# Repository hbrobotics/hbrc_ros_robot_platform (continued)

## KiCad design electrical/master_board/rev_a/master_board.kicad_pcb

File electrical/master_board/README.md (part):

<!--
MIT License

Copyright 2020 Home Brew Robotics Club

Permission is hereby granted, free of charge, to any person obtaining a copy of this
software and associated documentation files (the "Software"), to deal in the Software
without restriction, including without limitation the rights to use, copy, modify,
merge, publish, distribute, sublicense, and/or sell copies of the Software, and to
permit persons to whom the Software is furnished to do so, subject to the following
conditions:

The above copyright notice and this permission notice shall be included in all copies
or substantial portions of the Software.

THE SOFTWARE IS PROVIDED "AS IS", WITHOUT WARRANTY OF ANY KIND, EXPRESS OR IMPLIED,
INCLUDING BUT NOT LIMITED TO THE WARRANTIES OF MERCHANTABILITY, FITNESS FOR A PARTICULAR
PURPOSE AND NONINFRINGEMENT. IN NO EVENT SHALL THE AUTHORS OR COPYRIGHT HOLDERS BE LIABLE
FOR ANY CLAIM, DAMAGES OR OTHER LIABILITY, WHETHER IN AN ACTION OF CONTRACT, TORT OR
OTHERWISE, ARISING FROM, OUT OF OR IN CONNECTION WITH THE SOFTWARE OR THE USE OR OTHER
DEALINGS IN THE SOFTWARE.
-->
<!-- <<<<<<<<<<<<<<<<<<<<<<<<<<<<<<<<<<<<< 100 characters >>>>>>>>>>>>>>>>>>>>>>>>>>>>>>>>>>>>>> -->

# HR2 Master PCB Board

This is the common design information that is pretty applicable across all revisions
of the HR2 Master PCB Board.
The intention is to always use a higher end STM Nucleo-144 development board
as the embedded microcontroller.
This also allows processor upgrades to occur when newer Nucleo-144 boards come out
by simply upgrading to a newer Nucleo-144 board.
The higher end chips in the STM32Fxxx series of processors try to maintain peripheral
pin mappings across all versions of the 144-LQFP (144 pin Low profile Quad Flat Package.)
Time will tell how good ST Microelectronics is at adhering to this goal.
The nominal Nucleo-144 selected for revision A of the Master board is the Nucleo144-767ZI.
This may change over time with subsequent PCB board revisions.
g
It is a strong goal of the HR2 support the development of development boards that
plug onto the Nucleo-144.
The Nucleo-144 has two groups of connectors:

* Morpho Connectors:
  The Nucleo-144 has two Morpho connectors are called CN11 and CN12,
  each of which is a 2x35 pin connector.
  In general, the Morpho connectors connect to almost of the pins
  associated with STM32F microcontroller soldered to the Nucleo-144 board.
  The Nucleo-144 board ships without having either of the CN11 and CN12 connectors populated.
  It is necessary to solder connectors for CN11 and CN12.
  The HR2 master PCB sits under the Nucleo-144 and uses two female 2x35 headers to connect to the
  Nucleo-144 Morpho connectors.
  For the HR2, the Nucleo-144 is sufficiently big that it needs to positioned
  above the HR2 drive motors.
  For this reason, the Nucleo-144 needs long pins to bridge the distance
  between the CN11/CN12 connectors and to the master PCB.
  This is accomplished with two 2x35 male "wire-wrap" pin headers that are soldered to the
  bottom of the Nucleo-144 in CN11 and CN12.
  (Wire-wrap was a popular technology for prototyping electronics back in the 70's and 80's
  and it is still used occasionally to this day.)
  The Morpho connectors are exclusively dedicated to be used to connect the Nucleo-144
  to the HR2 master PCB.

* Zio Connectors:
  The Nucleo-144 has four Zio female pin connectors are called CN7 through CN10.
  These four connectors are sized and spaced to be compatible with Arduino shields.
  The difference is that while Arduino shields only use pin headers that are 1 wide,
  the Zio connectors are 2 pins wide.
  The extra row on each connector provides many more connectivity options
  than just simple Arduino pin connectors that are just 1 pin wide do.
  Despite these extra pins,
  the CN11/CN12 Morpho connectors still have pins than the CN7-CN10 Zio pins.

The ultimate goal of the HR2 is to support daughter boards that plug onto the Zio connectors.

The are 4 classes of daughter boards supported by the HR2.
Two of these classes use the Zio connectors and two do not.

* Arduino Shields (uses Zio connectors):
  An Arduino shield has 3 categories of pins:

  * Power/Miscellaneous Pins:
    The power and miscellaneous pins are RESET, 3.3V, 5V, GND, and VIN.
    These pins are easy to deal with and are not really mentioned any further in this document.

  * Digital Pins:
    There are 18 digital I/O pins named D0-D15.

  * Analog Pins:
    There 6 "analog" pins named A0-A5 that can used as analog-to-digital inputs
    or as digital I/O pins.
    Two of the "analog" pins (D4 and D5) are connected to an I2C peripheral.

  There are literally hundreds of Arduino shields that have been developed over the years.
  While  many of these Arduino shields are pretty mediocre, some of them are quite excellent.

* FPGA Daughter Board (uses Zio connectors):
  An FPGA  (Field Programmable Gate Array) daughter board is a PCB with an FPGA chip on it.
  The goal is to either allow the FPGA to totally control the robot or to partially control
  the robot in conjunction with the Nucleo-144 microcontroller.
  In addition, there is no particular reason why the FPGA should not be able to additionally host
  an Arduino shield on top if it so desires.

* Mikrobus Click Boards (does not use Zio connectors):

  The MikroElectronica company has created 20-pin standard peripheral boards
  that is called the MikroBus Click boards.
  These boards power, I2C, SPI, UART, and other pins.
  The come in three sizes -- small, medium and large.
  These 25.4mm wide (i.e. 1 inch) and 28.6mm (small), 42.9mm (medium), and 57.15mm (large).
  The HR2 has 2 Mikrobus connectors -- one small and one medium.
  A large can be plugged into the medium MikroBus connector on the HR2,
  but it will stick out of the robot.
  There are literally hundreds of MikroBus boards.

* Seeed Studio Grove Boards (does not use Zio connectors):
  Seeed Studio has come up with a huge library of peripheral boards that use a 4-pin
  proprietary connector.
  Two of the pins are power and ground and the other two vary from board to board.
  They fall into three broad categories:

  * Digital/Analog I/O: 2 pins of either digital and/or analog input or output.
    
  * I2C bus: 2 pins of I2C bus.

  * Serial: 2 pins of serial I/O (i.e. RX/TX.)

  The are 7 locations to mount Grove boards on the HR2.

The bottom line is that there many expansion opportunities for the HR2.

The following pin terminology is introduced.

* Arduino Pins:
  The Arduino signal pins are the pins that are reserved to connect to an Arduino shield.
  As mentioned above,
  the pins are further sub-divided into "analog" pins (A0-A5), and "digital" pins (D0-D13).
  Note that the "analog" pins can be connected to an A/D converter,
  but they can also be used as digital I/O pins.
  Two of the "analog" pins are bound to an I2C peripheral.
  There are 6 "analog" pins and 14 "digital" pins, for a total of 20 Arduino pins.

* Daughter Pins:
  The daughter pins are the remaining signal pins on the Zio connectors that are not
  are not Arduino Pins.
  It turns out that there are 45 dauhgter pins.

* Morpho Pins:
  The Morpho pins are the signal pins that are routed to the Morpho connectors
  but not also routed to the Zio connectors.
  It turns out that there are 17 Morpho pins.

* Nucleo Pins:
  The Nucleo-144 development board connects also connects some of its signal wires
  to the Morpho/Zio connectors.
  This is to be expected.
  Most of these pins are for the Ethernet connector, USB connector, and the ST-link signals.
  With three exceptions, Nucleo pins only connect to the Morph pins mentioned immeidately above.
  The three exceptions are:

  * PA7:
    PA7 is connected to the Ethernet interface chip.
    If you want to use the Ethernet interface,
    you must not attempt to plug in an Arduino shield that also needs to use D11.

  * PB0:
    PB0 is connected to LED called LD1.
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
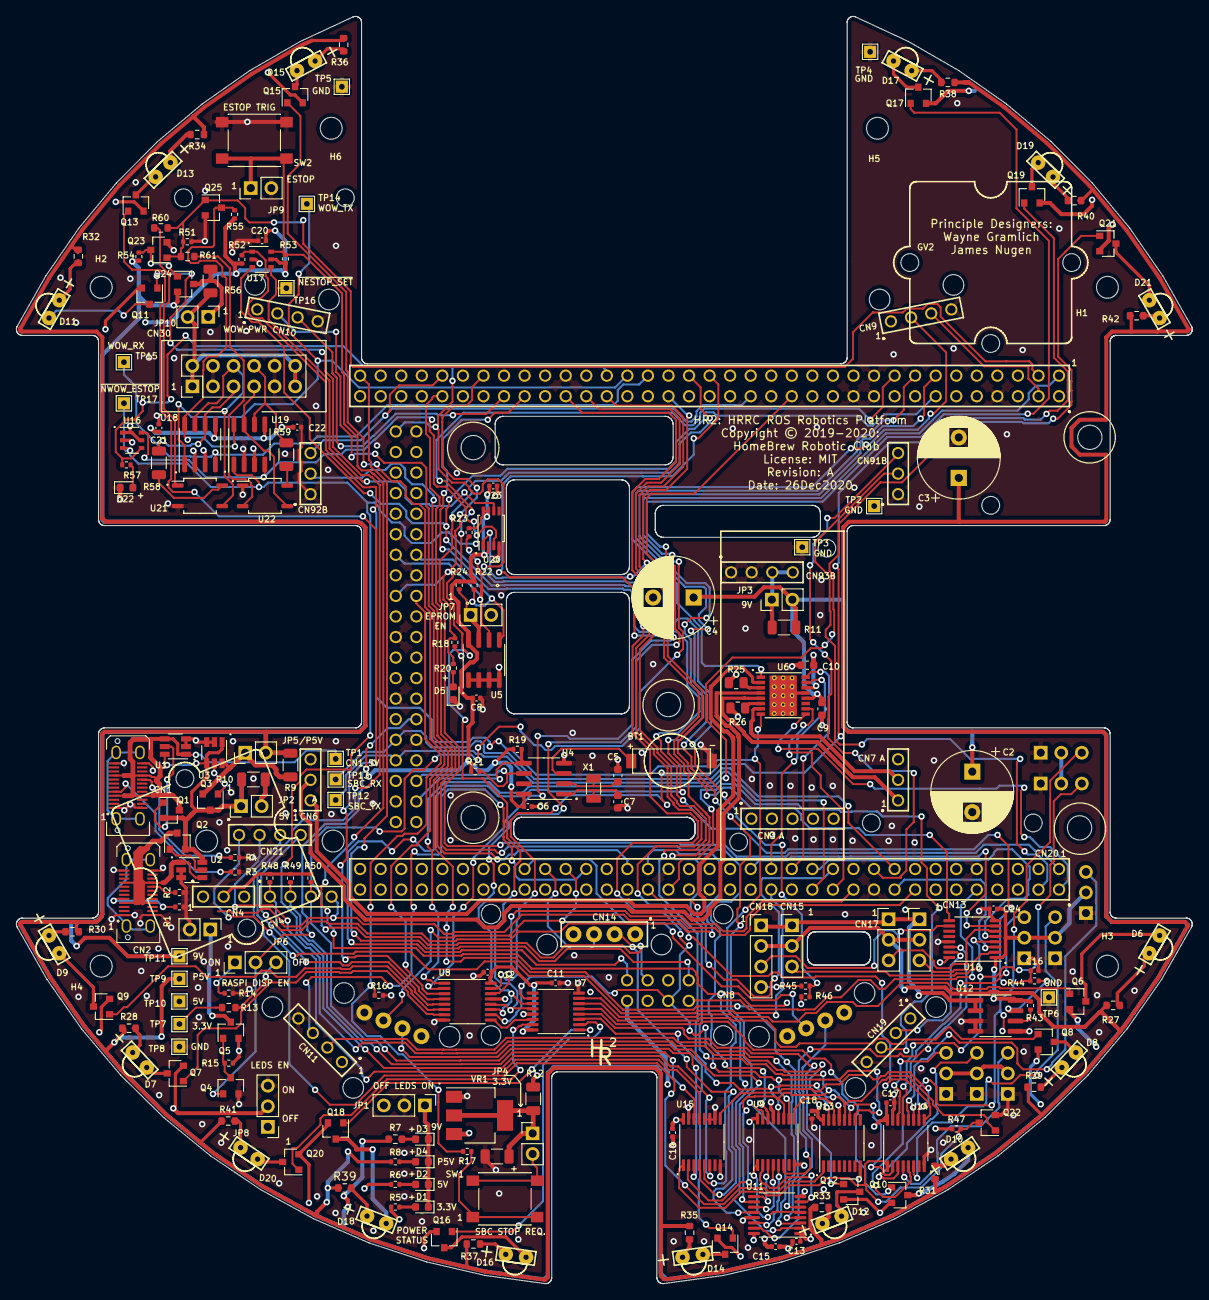
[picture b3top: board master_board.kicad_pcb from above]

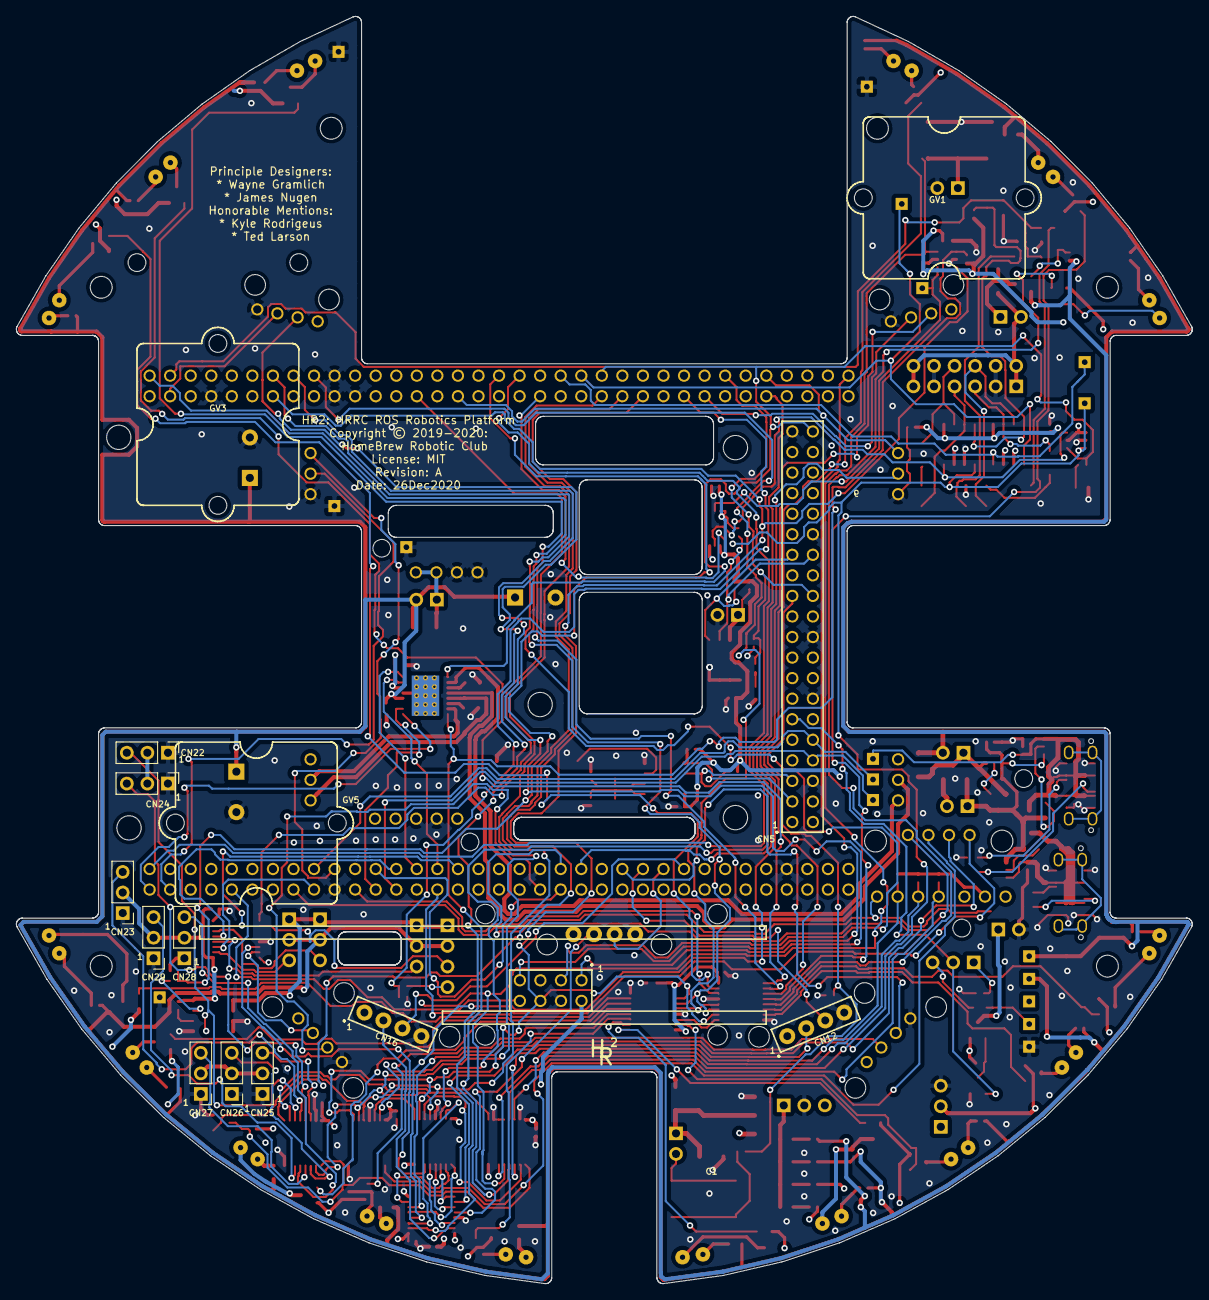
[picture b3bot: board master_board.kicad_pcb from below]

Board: 4 copper layers, 145.3 x 156.6 mm, 226 parts (13 on the bottom side), 198 nets.

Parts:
BT1: COIN_HOLDER6.8R;TE1376164-1; TE1376164-1_COINHOLDER6.8
C1: Ta22µF6.3V;3216; C_1206_3216Metric
C2, C4: 470µF,25Vmin;D10P5H13max; CP_Radial_D10.0mm_P5.00mm
C3: 1000µF@10Vmin;D10P5H13max; CP_Radial_D10.0mm_P5.00mm
C5, C7: 15pF;1608; C_0603_1608Metric
C6, C8, C11, C12, C13, C14, C15, C17, C18, C19, C20, C21, C22, C23: 0.1µF;1005; C_0402_1005Metric
C9: 10µF;1608; C_0603_1608Metric
C10: 2.2µF6.3V;1608; C_0603_1608Metric
C16: 0.01µF;1005; C_0402_1005Metric
CN1: USB-C;USB-C,POGND; USB_C_Receptacle_JAE_DX07S024WJ3R400
CN2: USB-C;USB-C; USB_C_Receptacle_JAE_DX07S024WJ3R400
CN3: POLOLU_U3V70F9;F1x4+F1x5; U3V70xMATE_F1x4+F1x5
CN4: RPI_DSP_PWR;M1x2; PinHeader_1x02_P2.54mm_Vertical
CN5: RASPI;F2X20; RASPI_F2X20
CN6, CN7: HR2_ENCODER;2xF1x3; ENCODER_2xF1x3
CN8: STADAPTER;F2x4; STADAPTER_F2x4
CN9, CN10: HCSR04LP;F1X4; HCSR04_F1x4H
CN11, CN19: HCSR04LP;F1X4; HCSR04_F1x4
CN12, CN14, CN16: HCSR04LP;F1X4; HCSR04_F1x4LP
CN13, CN15, CN17: SERVO;M1x3; PinHeader_1x03_P2.54mm_Vertical
CN18: SERVO;M1x4; PinHeader_1x04_P2.54mm_Vertical
CN20: NUCLEO-F767ZI;2xF2x35; NUCLEO_F767ZI_2xF2x35
CN21: LIDAR_ADAPTER;2xF1x4_F1x3; LIDAR_ADAPTER_2xF1x4_F1x3
CN22, CN23, CN24, CN25, CN26, CN27, CN28, CN29: SENSE;M1x3; PinHeader_1x03_P2.54mm_Vertical
CN30: WOW_OUT;M2x6S; PinHeader_2x06_P2.54mm_Vertical_Shrouded
D1, D2, D3, D4, D5: LEDGRN;1608; LED_0603_1608Metric
D6, D7, D8, D9, D10, D11, D12, D13, D14, D15, D16, D17, D18, D19, D20, D21: LED;GRNRA; LED_GRNRA
D22: REDLED;1608; LED_0603_1608Metric
GV1, GV2, GV3, GV4, GV5: GROVE;20x20; GROVE20x20
H1, H2, H3, H4, H5, H6: HOLE;M2.5; MountingHole_2.7mm_M2.5
JP1, JP8: LED_EN;M1x3; PinHeader_1x03_P2.54mm_Vertical
JP2, JP3, JP4, JP5, JP10: SHUNT;M1x2; PinHeader_1x02_P2.54mm_Vertical
JP6: RPI_DISP_EN;M1x3; PinHeader_1x03_P2.54mm_Vertical
JP7: JUMPER;M1x2; PinHeader_1x02_P2.54mm_Vertical
JP9: EXT_ESTOP;M1x2; PinHeader_1x02_P2.54mm_Vertical
Q1, Q2, Q3: NFET_3A_GSD;SOT23; SOT-23
Q4, Q6, Q7, Q8, Q9, Q10, Q11, Q12, Q13, Q14, Q15, Q16, Q17, Q18, Q19, Q20, Q21, Q22, Q23, Q25: 2N7002;SOT23; SOT-23
Q5, Q24: PFET_6A_GSD;SOT23; SOT-23
R1, R2, R3, R4: 10KΩ;1005; R_0402_1005Metric
R5, R20: 33Ω;1005; R_0402_1005Metric
R6, R8: 220Ω;1005; R_0402_1005Metric
R7: 560Ω;1608; R_0603_1608Metric
R9, R10, R11, R12, R56: 0Ω;3216; R_1206_3216Metric
R13: 100KΩ;1608; R_0603_1608Metric
R14, R15, R16, R18, R19, R21, R22, R23, R24, R43, R47, R48, R49, R50, R51, R52, R53, R54, R55: 100KΩ;1005; R_0402_1005Metric
R17, R44: 1KΩ;1005; R_0402_1005Metric
R25, R26: .16Ω.25W;2012; R_0805_2012Metric
R27, R28, R29, R30, R31, R32, R33, R34, R35, R36, R37, R38, R39, R40, R41, R42: 270Ω;1608; R_0603_1608Metric
R45: 2.2KΩ;1005; R_0402_1005Metric
R46: 3.3KΩ;1005; R_0402_1005Metric
R57: 120Ω;1005; R_0402_1005Metric
R58, R59: 120Ω.25W;3216; R_1206_3216Metric
R60, R61: 300Ω;1608; R_0603_1608Metric
SW1, SW2: BUTTON;6x6; SW_Push_1P1T_NO_6x6mm_H9.5mm
TP1: USB5V; TestPoint_THTPad_1.5x1.5mm_Drill0.7mm
TP2, TP3, TP4, TP5, TP6, TP8: GND; TestPoint_THTPad_1.5x1.5mm_Drill0.7mm
TP7: 3.3V; TestPoint_THTPad_1.5x1.5mm_Drill0.7mm
TP9: P5V; TestPoint_THTPad_1.5x1.5mm_Drill0.7mm
TP10: 5V; TestPoint_THTPad_1.5x1.5mm_Drill0.7mm
TP11: 9V; TestPoint_THTPad_1.5x1.5mm_Drill0.7mm
TP12: SPC_TX;M1x2; TestPoint_THTPad_1.5x1.5mm_Drill0.7mm
TP13: SBC_RX;M1x2; TestPoint_THTPad_1.5x1.5mm_Drill0.7mm
TP14: WOW_TX;M1x1; TestPoint_THTPad_1.5x1.5mm_Drill0.7mm
TP15: WOW_RX;M1x1; TestPoint_THTPad_1.5x1.5mm_Drill0.7mm
TP16: ~nESTOP_SET; TestPoint_THTPad_1.5x1.5mm_Drill0.7mm
TP17: ~nWOW_ESTOP;M1x1; TestPoint_THTPad_1.5x1.5mm_Drill0.7mm
U1, U2, U3: LM5050-1;TSOT-23-6; TSOT-23-6
U4: MCP7940;SOIC8; SOIC-8_3.9x4.9mm_P1.27mm
U5: CAT24C32;SOIC8; SOIC-8_3.9x4.9mm_P1.27mm
U6: DRV8833PWPR;HTSSOP16EP3.4x5; HTSSOP-16-1EP_4.4x5mm_P0.65mm_EP3.4x5mm_Mask3x3mm_ThermalVi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
U7, U8, U9, U13: SN74HC595;TSSOP16; TSSOP-16_4.4x5mm_P0.65mm
U10, U11: CD4504B;TTSOP16; TSSOP-16_4.4x5mm_P0.65mm
U12: ACS711;SOIC8; SOIC-8_3.9x4.9mm_P1.27mm
U14, U15: SN74HC165;TSSOP16; TSSOP-16_4.4x5mm_P0.65mm
U16, U17: 74x11G1;TSOP6; TSOP-6_1.65x3.05mm_P0.95mm
U18, U19: MCP2542;SOIC8; SOIC-8_3.9x4.9mm_P1.27mm
U20: 74LVC1G74;TSSOP8; TSSOP-8_3x3mm_P0.65mm
U21, U22: CPC1017N;SOP4W3.8L4.1; SOP-4_3.8x4.1mm_P2.54mm
VR1: AMS1117-3.3V800mA_GOI;SOT223; SOT-223-3_TabPin2
X1: 32.768kHz12.5pF;3.2x1.5; Crystal_SMD_3215-2Pin_3.2x1.5mm

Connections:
/3.3V: C6.1, C8.2, C11.1, C12.1, C13.1, C14.1, C15.1, C17.1, C18.1, C19.1, C20.2, C21.2, C22.2, C23.2, CN8.1, CN21.2, CN22.2, CN23.2, CN24.2, CN25.2, CN26.2, CN27.2, CN28.2, CN29.2, JP4.2, R5.1, R12.2, R13.1, R19.1, R21.1, R22.1, R23.1, R24.1, R43.1, R47.1, R48.1, R49.1, R50.1, R52.1, R53.1, R55.1, SW1.2, TP7.1, U4.8, U5.8, U7.16, U8.16, U9.16, U10.1, U11.1, U12.8, U13.16, U14.16, U15.16, U16.1, U16.5, U17.5, U18.5, U19.5, U20.2, U20.7, U20.8
/5V: CN3.4, CN3.5, CN5.2, CN5.4, CN6.3, CN7.3, CN9.1, CN10.1, CN11.1, CN12.1, CN14.1, CN16.1, CN19.1, CN20.1124, CN20.1207, CN21.1, JP2.2, Q5.2, R6.1, R10.2, R15.1, TP10.1, U10.16, U11.16, U18.3, U19.3, VR1.3
/9V: C2.1, C4.1, C9.1, JP3.2, Q24.2, R7.1, R11.2, R54.1, TP11.1, U6.12
/Connectors/DIO_IN_BRIDGE: U14.10, U15.9
/Connectors/DIO_SS: Q22.3, R47.2, U14.1, U15.1
/Connectors/LDR_EN: CN21.10, U13.1
/Connectors/LDR_ID0: CN21.4, R48.2, U15.13
/Connectors/LDR_ID1: CN21.5, R49.2, U15.14
/Connectors/LDR_ID2: CN21.6, R50.2, U15.3
/Connectors/LDR_SPIN: CN21.9, U13.15
/Connectors/SIG1: CN22.3, U14.11
/Connectors/SIG2: CN23.3, U14.12
/Connectors/SIG3: CN24.3, U14.13
/Connectors/SIG4: CN25.3, U14.14
/Connectors/SIG5: CN26.3, U14.3
/Connectors/SIG6: CN27.3, U14.4
/Connectors/SIG7: CN28.3, U14.5
/Connectors/SIG8: CN29.3, U14.6
/DIO_MISO: CN20.1150, U14.9
/DIO_MOSI: CN20.1162, U9.14
/DIO_SCK: CN20.1146, U9.11, U13.11, U14.2, U15.2
/ECHO1: CN9.3, CN20.1104
/ECHO2: CN10.3, CN20.1156
/ECHO3: CN11.3, CN20.1247
/ECHO4: CN12.3, CN20.1249
/ECHO5: CN14.3, CN20.1251
/ECHO6: CN16.3, CN20.1253
/ECHO7: CN19.3, CN20.1240
/ESTOP_CLR: CN20.1140, U20.1
/GND: BT1.2, C1.2, C2.2, C3.2, C4.2, C5.2, C6.2, C7.2, C8.1, C9.2, C10.2, C11.2, C12.2, C13.2, C14.2, C15.2, C16.2, C17.2, C18.2, C19.2, C20.1, C21.1, C22.1, C23.1, CN1.A1, CN1.A12, CN1.B1, CN1.B12, CN2.A1, CN2.A12, CN2.B1, CN2.B12, CN3.2, CN3.3, CN3.6, CN3.7, CN4.2, CN5.6, CN5.9, CN5.14, CN5.20, CN5.25, CN5.30, CN5.34, CN5.39, CN6.4, CN7.4, CN8.3, CN9.4, CN10.4, CN11.4, CN12.4, CN14.4, CN16.4, CN19.4, CN20.1108, CN20.1119, CN20.1120, CN20.1122, CN20.1149, CN20.1160, CN20.1209, CN20.1220, CN20.1232, CN20.1239, CN20.1254, CN20.1263, CN21.3, CN22.1, CN23.1, CN24.1, CN25.1, CN26.1, CN27.1, CN28.1, CN29.1, CN30.3, CN30.4, CN30.9, CN30.10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
/LDR_PWM: CN20.1241, CN21.11
/LDR_RX: CN20.1230, CN21.8
/LDR_TX: CN20.1216, CN21.7
/LED's/LED1: Q21.1, U8.15
/LED's/LED2: Q19.1, U8.1
/LED's/LED3: Q17.1, U8.2
/LED's/LED4: Q15.1, U8.3
/LED's/LED5: Q13.1, U8.4
/LED's/LED6: Q11.1, U8.5
/LED's/LED7: Q9.1, U8.6
/LED's/LED8: Q7.1, U8.7
/LED's/LED8_SER: U7.14, U8.9
/LED's/LED9: Q20.1, U7.15
/LED's/LED10: Q18.1, U7.1
/LED's/LED11: Q16.1, U7.2
/LED's/LED12: Q14.1, U7.3
/LED's/LED13: Q12.1, U7.4
/LED's/LED14: Q10.1, U7.5
/LED's/LED15: Q8.1, U7.6
/LED's/LED16: Q6.1, U7.7
/LED's/LEDS_GND: JP8.2, Q6.2, Q7.2, Q8.2, Q9.2, Q10.2, Q11.2, Q12.2, Q13.2, Q14.2, Q15.2, Q16.2, Q17.2, Q18.2, Q19.2, Q20.2, Q21.2
/LEDS_MOSI: CN20.1222, U8.14
/LEDS_SCLK: CN20.1101, U7.11, U8.11
/LMOTOR_CTL1: CN20.1227, U6.16
/LMOTOR_CTL2: CN20.1229, U6.15
/LQUAD_A: CN6.5, CN20.1243
/LQUAD_B: CN6.6, CN20.1132, CN20.1161
/Motors_Encoders/BMOTOR_OUT1: CN7.2, U6.7
/Motors_Encoders/BMOTOR_OUT2: CN7.1, U6.5
/Motors_Encoders/BMOTOR_SEN: R26.2, U6.6
/Motors_Encoders/LMOTOR_OUT1: CN6.1, U6.2
/Motors_Encoders/LMOTOR_OUT2: CN6.2, U6.4
/Motors_Encoders/LMOTOR_SEN: R25.2, U6.3
/P5V: C3.1, CN13.2, CN15.2, CN17.2, CN18.2, JP5.2, R8.1, R9.2, R27.1, R28.1, R29.1, R30.1, R31.1, R32.1, R33.1, R34.1, R35.1, R36.1, R37.1, R38.1, R39.1, R40.1, R41.1, R42.1, TP9.1
/Power/3.3V_LED: D1.2, R5.2
/Power/5V_LED: D2.2, R6.2
/Power/9V_LED: D3.2, R7.2
/Power/CN1_5V: CN1.A4, CN1.A9, CN1.B4, CN1.B9, Q1.3, TP1.1, U1.1, U1.4
/Power/CN2_5V: CN2.A4, CN2.A9, CN2.B4, CN2.B9, Q2.3, U2.1, U2.4
/Power/GATE1: Q1.1, U1.5
/Power/GATE2: Q2.1, U2.5
/Power/GATE3: Q3.1, U3.5
/Power/P5V_LED: D4.2, R8.2
/Power/SHUNT_3.3: C1.1, JP4.1, R12.1, VR1.2
/Power/SHUNT_5V: JP2.1, Q1.2, Q2.2, Q3.3, R10.1, U1.6, U2.6, U3.1, U3.4
/Power/SHUNT_9V: CN3.8, CN3.9, JP3.1, R11.1
/Power/SHUNT_P5V: JP5.1, Q3.2, R9.1, U3.6
/RMOTOR_CTL1: CN20.1202, U6.9
/RMOTOR_CTL2: CN20.1224, U6.10
/RQUAD_A: CN7.5, CN20.1204
/RQUAD_B: CN7.6, CN20.1219
/SBC_ALIVE: CN5.24, CN20.1157, R18.1, R20.1
/SERVO1: CN20.1128, U10.9
/SERVO2: CN20.1231, U10.7
/SERVO3: CN20.1225, U10.5
/SERVO4: CN20.1218, U10.3
/SERVO_CUR: C16.1, CN20.1135, R44.1
/SERVO_POS: CN20.1154, R45.2, R46.1
/SER_IO: U9.9, U13.14
/SPBC_RX: CN5.10, CN20.1217, TP13.1
/SPBC_TX: CN5.8, CN20.1226, TP12.1
/STL_RX: CN8.7, CN20.1210
/STL_TX: CN8.8, CN20.1169
/SWCLK: CN8.2, CN20.1115
/SWDIO: CN8.4, CN20.1113
/Single Board Computer/ID_SCL: CN5.28, R23.2, U5.6
/Single Board Computer/ID_SDA: CN5.27, R22.2, U5.5
/Single Board Computer/RPI_DSP_EN: CN5.11, JP6.2, Q4.1
/Single Board Computer/SBC_REQ: R17.1, SW1.1
/Single Board Computer/SBC_SCL: CN5.5, R21.2, U4.6
/Single Board Computer/SBC_SDA: CN5.3, R19.2, U4.5
/Single Board Computer/SBC_STOP: CN5.23, R16.1, R17.2
/Single Board Computer/VBAT: BT1.1, U4.3
/Single Board Computer/WP: JP7.1, R24.2, U5.7
/Single Board Computer/X1: C7.1, U4.1, X1.2
/Single Board Computer/X2: C5.1, U4.2, X1.1
/Sonars and Servos/SERVO1_5V: CN18.3, U10.10
/Sonars and Servos/SERVO2_5V: CN17.3, U10.6
/Sonars and Servos/SERVO3_5V: CN15.3, U10.4
/Sonars and Servos/SERVO4_5V: CN13.3, U10.2
/Sonars and Servos/SGND: CN13.1, CN15.1, CN17.1, CN18.1, U12.1, U12.2
/Sonars and Servos/TRIG1: U9.15, U11.3
/Sonars and Servos/TRIG1_5V: CN9.2, U11.2
/Sonars and Servos/TRIG2: U9.1, U11.5
/Sonars and Servos/TRIG2_5V: CN10.2, U11.4
/Sonars and Servos/TRIG3: U9.2, U11.7
/Sonars and Servos/TRIG3_5V: CN11.2, U11.6
/Sonars and Servos/TRIG4: U9.3, U11.9
/Sonars and Servos/TRIG4_5V: CN12.2, U11.10
/Sonars and Servos/TRIG5: U9.4, U11.11
/Sonars and Servos/TRIG5_5V: CN14.2, U11.12
/Sonars and Servos/TRIG6: U9.5, U11.14
/Sonars and Servos/TRIG6_5V: CN16.2, U11.15
/Sonars and Servos/TRIG7: U9.6, U10.14
/Sonars and Servos/TRIG7_5V: CN19.2, U10.15
/WOWBus/WOW_COMH: CN30.6, U18.7, U21.3
/WOWBus/WOW_COML: CN30.5, R58.2, U18.6
/WOWBus/WOW_COM_OPTO: R60.1, U21.1
/WOWBus/WOW_ESTOP_OPTO: R61.2, U22.2
/WOWBus/WOW_POW_OUT: CN30.1, CN30.2, CN30.11, CN30.12, JP10.2, R56.2
/WOWBus/WOW_STDBY: Q25.3, R55.2, U18.8, U19.8
/WOWBus/WOW_STOPH: CN30.7, U19.7, U22.3
/WOWBus/WOW_STOPL: CN30.8, R59.2, U19.6
/WOWBus/~NESTOP_SET: TP16.1, U17.4, U20.6
/WOWBus/~NHR2_ESTOP: U16.6, U19.4, U20.3
/WOWBus/~NWOW_EN: Q23.3, Q24.1, R54.2
/WOW_EN: CN20.1103, Q23.1, Q25.1, R51.1, R60.2, R61.1
/WOW_RX: CN20.1141, TP15.1, U18.4
/WOW_TX: CN20.1143, TP14.1, U18.1
/~DIO_NSS: CN20.1148, Q22.1, U9.12, U13.12
/~LEDS_NSS: CN20.1117, U7.12, U8.12
/~NBTN_ESTOP: JP9.1, R53.2, SW2.2, U15.5, U17.6
/~NESTOP: CN5.40, CN20.1145, R57.1, U6.1, U16.4
/~NMOTOR_FAULT: R52.2, U6.8, U15.4, U17.1
/~NRST: CN8.5, CN20.1114, U7.10, U8.10, U9.10, U13.10, U17.3
/~NWOW_ESTOP: TP17.1, U15.6, U16.3, U19.1
unnamed: C10.1, U6.14
unnamed: CN1.A5, R3.2
unnamed: CN1.B5, R4.2
unnamed: CN2.A5, R1.2
unnamed: CN2.B5, R2.2
unnamed: CN4.1, Q5.3
unnamed: CN18.4, R45.1
unnamed: CN20.1137, CN20.1201
unnamed: CN20.1223, CN20.1242
unnamed: D1.1, D2.1, D3.1, D4.1, JP1.1
unnamed: D5.2, R20.2
unnamed: D6.1, Q6.3
unnamed: D6.2, R27.2
unnamed: D7.1, Q7.3
unnamed: D7.2, R28.2
unnamed: D8.1, Q8.3
unnamed: D8.2, R29.2
unnamed: D9.1, Q9.3
unnamed: D9.2, R30.2
unnamed: D10.1, Q10.3
unnamed: D10.2, R31.2
unnamed: D11.1, Q11.3
unnamed: D11.2, R32.2
unnamed: D12.1, Q12.3
unnamed: D12.2, R33.2
unnamed: D13.1, Q13.3
unnamed: D13.2, R34.2
unnamed: D14.1, Q14.3
unnamed: D14.2, R35.2
unnamed: D15.1, Q15.3
unnamed: D15.2, R36.2
unnamed: D16.1, Q16.3
unnamed: D16.2, R37.2
unnamed: D17.1, Q17.3
unnamed: D17.2, R38.2
unnamed: D18.1, Q18.3
unnamed: D18.2, R39.2
unnamed: D19.1, Q19.3
unnamed: D19.2, R40.2
unnamed: D20.1, Q20.3
unnamed: D20.2, R41.2
unnamed: D21.1, Q21.3
unnamed: D21.2, R42.2
unnamed: D22.2, R57.2
unnamed: JP6.1, R14.1
unnamed: JP6.3, R13.2
unnamed: JP10.1, Q24.3, R56.1
unnamed: Q4.3, Q5.1, R15.2
unnamed: R43.2, U12.6
unnamed: R44.2, U12.7
unnamed: R58.1, U21.4
unnamed: R59.1, U22.4

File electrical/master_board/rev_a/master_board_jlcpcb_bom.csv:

"Comment","Designator","Footprint","LCSC Part #"
"Ta22uF6.3V;3216","C1, ","CASE-A","C135574",
"2.2uF6.3V;1608","C10, ","0603","C23630",
"0.01uF;1005","C16, ","0402","C15195",
"15pF;1608","C5, C7, ","0603","C1644",
"0.1uF;1005","C6, C8, C11, C12, C13, C14, C15, C17, C18, C19, C20, C21, C22, C23, ","0402","C1525",
"10uF;1608","C9, ","0603","C19702",
"LEDGRN;1608","D1, D2, D3, D4, D5, ","LED_0603","C72043",
"REDLED;1608","D22, ","LED_0603","C2286",
"NFET_3A_GSD;SOT23","Q1, Q2, Q3, ","SOT-23-3L","C20917",
"2N7002;SOT23","Q4, Q6, Q7, Q8, Q9, Q10, Q11, Q12, Q13, Q14, Q15, Q16, Q17, Q18, Q19, Q20, Q21, Q22, Q23, Q25, ","SOT-23-3","C8545",
"PFET_6A_GSD;SOT23","Q5, Q24, ","SOT-23-3","C141546",
"10KOhm;1005","R1, R2, R3, R4, ","0402","C25744",
"100KOhm;1608","R13, ","0603","C25803",
"100KOhm;1005","R14, R15, R16, R18, R19, R21, R22, R23, R24, R43, R47, R48, R49, R50, R51, R52, R53, R54, R55, ","0402","C25741",
"1KOhm;1005","R17, R44, ","0402","C11702",
".16Ohm.25W;2012","R25, R26, ","0805","C34388",
"270Ohm;1608","R27, R28, R29, R30, R31, R32, R33, R34, R35, R36, R37, R38, R39, R40, R41, R42, ","0603","C22966",
"2.2KOhm;1005","R45, ","0402","C25879",
"3.3KOhm;1005","R46, ","0402","C25890",
"33Ohm;1005","R5, R20, ","0402","C25105",
"120Ohm;1005","R57, ","0402","C25079",
"120Ohm.25W;3216","R58, R59, ","1206","C17909",
"220Ohm;1005","R6, R8, ","0402","C25091",
"300Ohm;1608","R60, R61, ","0603","C23025",
"560Ohm;1608","R7, ","0603","C23204",
"0Ohm;3216","R9, R10, R11, R12, R56, ","1206","C17888",
"BUTTON;6x6","SW1, SW2, ","SMD-4","C127509",
"LM5050-1;TSOT-23-6","U1, U2, U3, ","SOT-23-6L","C55266",
"CD4504B;TTSOP16","U10, U11, ","TSSOP-16","C233582",
"ACS711;SOIC8","U12, ","SOIC-8","C10681",
"SN74HC165;TSSOP16","U14, U15, ","HTSSOP-16","C201716",
"CPC1017N;SOP4W3.8L4.1","U21, U22, ","SOP-4","C261926",
"MCP7940;SOIC8","U4, ","SOIC-8","C7440",
"CAT24C32;SOIC8","U5, ","SOIC-8","C81193",
"DRV8833PWPR;HTSSOP16EP3.4x5","U6, ","HTSSOP-16","C50506",
"SN74HC595;TSSOP16","U7, U8, U9, U13, ","HTSSOP-16","C5948",
"AMS1117-3.3V800mA_GOI;SOT223","VR1, ","SOT-223","C6186",
"32.768kHz12.5pF;3.2x1.5","X1, ","SMD-3215","C32346",

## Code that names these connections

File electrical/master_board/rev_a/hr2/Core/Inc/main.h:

/* USER CODE BEGIN Header */
/**
  ******************************************************************************
  * @file           : main.h
  * @brief          : Header for main.c file.
  *                   This file contains the common defines of the application.
  ******************************************************************************
  * @attention
  *
  * <h2><center>&copy; Copyright (c) 2020 STMicroelectronics.
  * All rights reserved.</center></h2>
  *
  * This software component is licensed by ST under BSD 3-Clause license,
  * the "License"; You may not use this file except in compliance with the
  * License. You may obtain a copy of the License at:
  *                        opensource.org/licenses/BSD-3-Clause
  *
  ******************************************************************************
  */
/* USER CODE END Header */

/* Define to prevent recursive inclusion -------------------------------------*/
#ifndef __MAIN_H
#define __MAIN_H

#ifdef __cplusplus
extern "C" {
#endif

/* Includes ------------------------------------------------------------------*/
#include "stm32f7xx_hal.h"

/* Private includes ----------------------------------------------------------*/
/* USER CODE BEGIN Includes */

/* USER CODE END Includes */

/* Exported types ------------------------------------------------------------*/
/* USER CODE BEGIN ET */

/* USER CODE END ET */

/* Exported constants --------------------------------------------------------*/
/* USER CODE BEGIN EC */

/* USER CODE END EC */

/* Exported macro ------------------------------------------------------------*/
/* USER CODE BEGIN EM */

/* USER CODE END EM */

/* Exported functions prototypes ---------------------------------------------*/
void Error_Handler(void);

/* USER CODE BEGIN EFP */

/* USER CODE END EFP */

/* Private defines -----------------------------------------------------------*/
#define DIO_SCK_Pin GPIO_PIN_2
#define DIO_SCK_GPIO_Port GPIOE
#define DIO_NSS_Pin GPIO_PIN_4
#define DIO_NSS_GPIO_Port GPIOE
#define DIO_MOSO_Pin GPIO_PIN_5
#define DIO_MOSO_GPIO_Port GPIOE
#define DIO_MOSI_Pin GPIO_PIN_6
#define DIO_MOSI_GPIO_Port GPIOE
#define USER_BTN_Pin GPIO_PIN_13
#define USER_BTN_GPIO_Port GPIOC
#define MISC_SDA_Pin GPIO_PIN_0
#define MISC_SDA_GPIO_Port GPIOF
#define MISC_SCL_Pin GPIO_PIN_1
#define MISC_SCL_GPIO_Port GPIOF
#define A3_Pin GPIO_PIN_3
#define A3_GPIO_Port GPIOF
#define A4_SDA_Pin GPIO_PIN_5
#define A4_SDA_GPIO_Port GPIOF
#define FPGA_RX_Pin GPIO_PIN_7
#define FPGA_RX_GPIO_Port GPIOF
#define SERVO_POS_Pin GPIO_PIN_8
#define SERVO_POS_GPIO_Port GPIOF
#define ECHO2_Pin GPIO_PIN_9
#define ECHO2_GPIO_Port GPIOF
#define A5_SCL_Pin GPIO_PIN_10
#define A5_SCL_GPIO_Port GPIOF
#define MCO_Pin GPIO_PIN_0
#define MCO_GPIO_Port GPIOH
#define A1_Pin GPIO_PIN_0
#define A1_GPIO_Port GPIOC
#define RMII_MDC_Pin GPIO_PIN_1
#define RMII_MDC_GPIO_Port GPIOC
#define SERVO_CUR_Pin GPIO_PIN_2
#define SERVO_CUR_GPIO_Port GPIOC
#define A2_Pin GPIO_PIN_3
#define A2_GPIO_Port GPIOC
#define SERVO1_Pin GPIO_PIN_0
#define SERVO1_GPIO_Port GPIOA
#define RMII_REF_CLK_Pin GPIO_PIN_1
#define RMII_REF_CLK_GPIO_Port GPIOA
#define RMII_MDIO_Pin GPIO_PIN_2
#define RMII_MDIO_GPIO_Port GPIOA
#define A0_Pin GPIO_PIN_3
#define A0_GPIO_Port GPIOA
#define LQUAD_B_Pin GPIO_PIN_4
#define LQUAD_B_GPIO_Port GPIOA
#define D13_SCK_Pin GPIO_PIN_5
#define D13_SCK_GPIO_Port GPIOA
#define D12_MISO_Pin GPIO_PIN_6
#define D12_MISO_GPIO_Port GPIOA
#define D11_PWM_MOSI_Pin GPIO_PIN_7
#define D11_PWM_MOSI_GPIO_Port GPIOA
#define RMII_RXD0_Pin GPIO_PIN_4
#define RMII_RXD0_GPIO_Port GPIOC
#define RMII_RXD1_Pin GPIO_PIN_5
#define RMII_RXD1_GPIO_Port GPIOC
#define GRN_LED_Pin GPIO_PIN_0
#define GRN_LED_GPIO_Port GPIOB
#define RMOTOR_CTL2_Pin GPIO_PIN_1
#define RMOTOR_CTL2_GPIO_Port GPIOB
#define LEDS_MOSI_Pin GPIO_PIN_2
#define LEDS_MOSI_GPIO_Port GPIOB
#define FPGA_TX_Pin GPIO_PIN_7
#define FPGA_TX_GPIO_Port GPIOE
#define ECHO7_Pin GPIO_PIN_8
#define ECHO7_GPIO_Port GPIOE
#define D6_PWM_Pin GPIO_PIN_9
#define D6_PWM_GPIO_Port GPIOE
#define ECHO3_Pin GPIO_PIN_10
#define ECHO3_GPIO_Port GPIOE
#define D5_PWM_Pin GPIO_PIN_11
#define D5_PWM_GPIO_Port GPIOE
#define ECHO4_Pin GPIO_PIN_12
#define ECHO4_GPIO_Port GPIOE
#define D3_PWM_Pin GPIO_PIN_13
#define D3_PWM_GPIO_Port GPIOE
#define ECHO5_Pin GPIO_PIN_14
#define ECHO5_GPIO_Port GPIOE
#define ECHO6_Pin GPIO_PIN_15
#define ECHO6_GPIO_Port GPIOE
#define SERVO3_Pin GPIO_PIN_10
#define SERVO3_GPIO_Port GPIOB
#define SERVO4_Pin GPIO_PIN_11
#define SERVO4_GPIO_Port GPIOB
#define LIDAR_TX_Pin GPIO_PIN_12
#define LIDAR_TX_GPIO_Port GPIOB
#define LIDAR_RX_Pin GPIO_PIN_13
#define LIDAR_RX_GPIO_Port GPIOB
#define LD3_Pin GPIO_PIN_14
#define LD3_GPIO_Port GPIOB
#define SBC_TX_Pin GPIO_PIN_15
#define SBC_TX_GPIO_Port GPIOB
#define STL_RX_Pin GPIO_PIN_8
#define STL_RX_GPIO_Port GPIOD
#define STL_TX_Pin GPIO_PIN_9
#define STL_TX_GPIO_Port GPIOD
#define LQUAD_A_Pin GPIO_PIN_12
#define LQUAD_A_GPIO_Port GPIOD
#define LIDAR_PWM_Pin GPIO_PIN_13
#define LIDAR_PWM_GPIO_Port GPIOD
#define D10_PWM_NSS_Pin GPIO_PIN_14
#define D10_PWM_NSS_GPIO_Port GPIOD
#define D9_PWM_Pin GPIO_PIN_15
#define D9_PWM_GPIO_Port GPIOD
#define USB_PowerSwitchOn_Pin GPIO_PIN_6
#define USB_PowerSwitchOn_GPIO_Port GPIOG
#define USB_OverCurrent_Pin GPIO_PIN_7
#define USB_OverCurrent_GPIO_Port GPIOG
#define RQUAD_A_Pin GPIO_PIN_6
#define RQUAD_A_GPIO_Port GPIOC
#define RQUAD_B_Pin GPIO_PIN_7
#define RQUAD_B_GPIO_Port GPIOC
#define RMOTOR_CTL1_Pin GPIO_PIN_8
#define RMOTOR_CTL1_GPIO_Port GPIOC
#define A4_SDAC9_Pin GPIO_PIN_9
#define A4_SDAC9_GPIO_Port GPIOC
#define USB_VBUS__Pin GPIO_PIN_9
#define USB_VBUS__GPIO_Port GPIOA
#define USB_ID_Pin GPIO_PIN_10
#define USB_ID_GPIO_Port GPIOA
#define USB_DM_Pin GPIO_PIN_11
#define USB_DM_GPIO_Port GPIOA
#define USB_DP_Pin GPIO_PIN_12
#define USB_DP_GPIO_Port GPIOA
#define SWDIO_Pin GPIO_PIN_13
#define SWDIO_GPIO_Port GPIOA
#define SWCLK_Pin GPIO_PIN_14
#define SWCLK_GPIO_Port GPIOA
#define LEDS_NSS_Pin GPIO_PIN_15
#define LEDS_NSS_GPIO_Port GPIOA
#define LEDS_SCK_Pin GPIO_PIN_10
#define LEDS_SCK_GPIO_Port GPIOC
#define LEDS_MISO_Pin GPIO_PIN_11
#define LEDS_MISO_GPIO_Port GPIOC
#define WOW_EN_Pin GPIO_PIN_12
#define WOW_EN_GPIO_Port GPIOC
#define SBC_ALIVE_Pin GPIO_PIN_0
#define SBC_ALIVE_GPIO_Port GPIOD
#define INT1_Pin GPIO_PIN_1
#define INT1_GPIO_Port GPIOD
#define ECHO1_Pin GPIO_PIN_2
#define ECHO1_GPIO_Port GPIOD
#define ESTOP_CLR_Pin GPIO_PIN_3
#define ESTOP_CLR_GPIO_Port GPIOD
#define WOW_RX_Pin GPIO_PIN_5
#define WOW_RX_GPIO_Port GPIOD
#define WOW_TX_Pin GPIO_PIN_6
#define WOW_TX_GPIO_Port GPIOD
#define ESTOP_Pin GPIO_PIN_7
#define ESTOP_GPIO_Port GPIOD
#define D0_RX_Pin GPIO_PIN_9
#define D0_RX_GPIO_Port GPIOG
#define RMII_TX_EN_Pin GPIO_PIN_11
#define RMII_TX_EN_GPIO_Port GPIOG
#define RMII_TXD0_Pin GPIO_PIN_13
#define RMII_TXD0_GPIO_Port GPIOG
#define D1_TX_Pin GPIO_PIN_14
#define D1_TX_GPIO_Port GPIOG
#define SERVO2_Pin GPIO_PIN_3
#define SERVO2_GPIO_Port GPIOB
#define LMOTOR_CTL1_Pin GPIO_PIN_4
#define LMOTOR_CTL1_GPIO_Port GPIOB
#define LMOTOR_CTL2_Pin GPIO_PIN_5
#define LMOTOR_CTL2_GPIO_Port GPIOB
#define SBC_RX_Pin GPIO_PIN_6
#define SBC_RX_GPIO_Port GPIOB
#define BLUE_LED_Pin GPIO_PIN_7
#define BLUE_LED_GPIO_Port GPIOB
#define D15_Pin GPIO_PIN_8
#define D15_GPIO_Port GPIOB
#define D14_Pin GPIO_PIN_9
#define D14_GPIO_Port GPIOB
#define INT0_Pin GPIO_PIN_0
#define INT0_GPIO_Port GPIOE
#define LQUAD_BE1_Pin GPIO_PIN_1
#define LQUAD_BE1_GPIO_Port GPIOE
/* USER CODE BEGIN Private defines */

/* USER CODE END Private defines */

#ifdef __cplusplus
}
#endif

#endif /* __MAIN_H */

/************************ (C) COPYRIGHT STMicroelectronics *****END OF FILE****/

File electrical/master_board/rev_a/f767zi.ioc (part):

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PB13.GPIOParameters=GPIO_Label
PC7.GPIOParameters=GPIO_Label
PC12.Signal=UART5_TX
PB14.GPIO_Label=LD3 [Red]
PG6.GPIO_Label=USB_PowerSwitchOn [STMPS2151STR_EN]
PA14.GPIO_Label=TCK
PG3.GPIOParameters=GPIO_Label,GPIO_ModeDefaultOutputPP
PG0.Signal=GPIO_Output
PC6.GPIO_Label=LD_BEAM_EN
PB13.Signal=ETH_TXD1
PG13.Signal=ETH_TXD0
PG2.GPIOParameters=GPIO_Label,GPIO_ModeDefaultOutputPP
PG15.GPIO_Label=_ESTOP2
PG2.GPIO_ModeDefaultOutputPP=GPIO_MODE_OUTPUT_PP
PC7.Signal=GPIO_Output
PH1/OSC_OUT.Signal=RCC_OSC_OUT
PE1.Signal=UART8_TX
PF10.GPIO_Label=ESTOPPED
PB3.Mode=Trace_Asynchronous_SW
PF1.GPIO_Label=PCB_ID1
PG14.Mode=Asynchronous
PG1.GPIOParameters=GPIO_Label,GPIO_ModeDefaultOutputPP
PC4.GPIO_Label=RMII_RXD0 [LAN8742A-CZ-TR_RXD0]
PG12.GPIOParameters=GPIO_Label
PA8.Signal=USB_OTG_FS_SOF
PF3.Signal=GPIO_Input
PG0.GPIO_PuPd=GPIO_NOPULL
Mcu.Package=LQFP144
PG13.GPIOParameters=GPIO_Label
PA10.Signal=USART1_RX
PB14.GPIOParameters=GPIO_Label
PC4.GPIOParameters=GPIO_Label
PG12.Signal=GPIO_Input
PA15.GPIOParameters=GPIO_Label
PG9.Signal=USART6_RX
PC13.Signal=GPXTI13
PE1.Mode=Asynchronous
PG9.Mode=Asynchronous
PC6.Signal=GPIO_Output
PA11.GPIO_Label=USB_DM
PC11.GPIOParameters=GPIO_Label
PG13.GPIO_Label=RMII_TXD0 [LAN8742A-CZ-TR_TXD0]
PG10.Signal=GPIO_Output
PE8.Mode=Asynchronous
PA3.Mode=Asynchronous
PA8.GPIO_Label=USB_SOF [TP1]
PA9.Signal=USART1_TX
PB10.Signal=USART3_TX
PA0/WKUP.Mode=Asynchronous
PF3.GPIOParameters=GPIO_Label
PG6.GPIOParameters=GPIO_Label
PB14.Signal=GPIO_Output
PC12.Mode=Asynchronous
PF2.GPIOParameters=GPIO_Label
PA1.Mode=Asynchronous
PE8.Signal=UART7_TX
PG7.GPIO_Label=USB_OverCurrent [STMPS2151STR_FAULT]
PC10.GPIOParameters=GPIO_Label
PA13.Mode=Trace_Asynchronous_SW
PC9.GPIOParameters=GPIO_Label
PC7.GPIO_Label=LD_MTR_EN
PG15.GPIOParameters=GPIO_Label
PA14.GPIOParameters=GPIO_Label
PA11.Signal=USB_OTG_FS_DM
PF10.GPIOParameters=GPIO_Label
PF0.GPIO_Label=PCB_ID0
PG0.GPIOParameters=GPIO_PuPd,GPIO_Label,GPIO_ModeDefaultOutputPP
PC15/OSC32_OUT.Signal=RCC_OSC32_OUT
PG3.GPIO_Label=LED3
PD2.Signal=UART5_RX
PA7.GPIOParameters=GPIO_Label
PC1.Signal=ETH_MDC
PG10.GPIO_Label=_ESTOP0
PG7.GPIOParameters=GPIO_Label
PH0/OSC_IN.GPIOParameters=GPIO_Label
PG6.Signal=GPIO_Output
Mcu.UserName=STM32F767ZITx
PG2.Signal=GPIO_Output
PC10.Signal=GPIO_Output
RCC.SYSCLKSourceVirtual=RCC_SYSCLKSOURCE_PLLCLK
PF0.GPIOParameters=GPIO_Label
PA12.GPIOParameters=GPIO_Label
PA9.GPIOParameters=GPIO_PuPd,GPIO_Mode
PA11.GPIOParameters=GPIO_Label
PA0/WKUP.Signal=UART4_TX
PC13.GPIO_Label=USER_Btn [B1]
PB13.GPIO_Label=RMII_TXD1 [LAN8742A-CZ-TR_TXD1]
PB11.Signal=USART3_RX
PG11.Signal=GPIO_Output
PG15.Signal=GPIO_Input
PA15.GPIO_Label=_ESTOP_RESET
PA12.Signal=USB_OTG_FS_DP
PC1.GPIOParameters=GPIO_Label
PF1.GPIOParameters=GPIO_Label
PG3.GPIO_ModeDefaultOutputPP=GPIO_MODE_OUTPUT_PP
PF11.GPIO_Label=_ESTOP_BUS
PA8.GPIOParameters=GPIO_Label
PG0.GPIO_ModeDefaultOutputPP=GPIO_MODE_OUTPUT_PP
PA9.GPIO_Mode=GPIO_MODE_AF_PP
RCC.HSE_VALUE=16000000
PA14.Mode=Trace_Asynchronous_SW
PF11.Signal=GPIO_Input
PC11.GPIO_Label=LDR_RX
PB3.GPIOParameters=GPIO_Label
PB7.Signal=GPIO_Output
PF11.GPIOParameters=GPIO_Label
PA13.GPIOParameters=GPIO_Label
PB7.GPIO_Label=LD2 [Blue]
PC14/OSC32_IN.Signal=RCC_OSC32_IN
PA15.Signal=GPIO_Output
PG0.GPIO_Label=LED0
PG11.GPIO_Label=STBY
PF0.Signal=GPIO_Input
PC5.Signal=ETH_RXD1
PE7.Signal=UART7_RX
PF3.GPIO_Label=PCB_ID3
PG2.GPIO_Label=LED2
PA3.Signal=USART2_RX
PB3.GPIO_Label=SW0
PG7.Signal=GPIO_Input
PC10.GPIO_Label=LDR_TX
PA10.Mode=Asynchronous
PC9.GPIO_Label=_LPWR_DISABLE
PG3.Signal=GPIO_Output
PG1.Signal=GPIO_Output
PC11.Signal=GPIO_Input
PC8.Signal=S_TIM3_CH3
PC4.Signal=ETH_RXD0
boardIOC=true
PA9.GPIO_PuPd=GPIO_PULLUP
PA12.GPIO_Label=USB_DP
PA13.Signal=SYS_JTMS-SWDIO
PA9.Mode=Asynchronous
PB7.GPIOParameters=GPIO_Label
PC5.GPIOParameters=GPIO_Label
PF2.Signal=GPIO_Input
PG10.GPIOParameters=GPIO_Label
PG1.GPIO_ModeDefaultOutputPP=GPIO_MODE_OUTPUT_PP
PA1.Signal=UART4_RX
PD2.Mode=Asynchronous
PG14.Signal=USART6_TX
board=NUCLEO-F767ZI
PG1.GPIO_Label=LED1
PH0/OSC_IN.Signal=RCC_OSC_IN
PC13.GPIOParameters=GPIO_Label
PF10.Signal=GPIO_Input
PC1.GPIO_Label=RMII_MDC [LAN8742A-CZ-TR_MDC]
PF1.Signal=GPIO_Input
Mcu.Name=STM32F767ZITx
PE0.Signal=UART8_RX
PA2.Signal=USART2_TX
PA13.GPIO_Label=TMS
PB3.Signal=SYS_JTDO-SWO
RCC.SYSCLKFreq_VALUE=16000000
PE7.Mode=Asynchronous
PA7.GPIO_Label=RMII_CRS_DV [LAN8742A-CZ-TR_CRS_DV]
PC5.GPIO_Label=RMII_RXD1 [LAN8742A-CZ-TR_RXD1]
PA14.Signal=SYS_JTCK-SWCLK
PC6.GPIOParameters=GPIO_Label
PG12.GPIO_Label=_ESTOP1
PH0/OSC_IN.GPIO_Label=MCO [STM32F103CBT6_PA8]
PA2.Mode=Asynchronous
PC9.Signal=GPIO_Output
PE0.Mode=Asynchronous
PG11.GPIOParameters=GPIO_Label
PA7.Signal=ETH_CRS_DV
PF2.GPIO_Label=PCB_ID2

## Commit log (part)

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2020-04-19 Merged with master
2020-04-19 Fixed a bug in pre-commit.
2020-04-19 Added none option to hr2_install.
2020-04-20 Added --ff to git pull commands.
2020-04-20 Use $(...) instead of `...` syntax in hr2_install. Updated README.md .
2020-04-20 Fixed pre-push and pre-commit scripts.
2020-04-23 Tweak hr2_install to add HR2_DIRECTORY environment variable to ~/.bashrc .
2020-04-24 Added bin/.gitignore .
2020-04-25 Added some notes to electrical README.md.
2020-04-25 Added master_merge and repository_update shell scripts to bin directory.
2020-04-25 Updated top README.md to document the work flow scripts. Enhanced pull_request script.
2020-04-26 Cleaned up some file in the me directory.
2020-04-27 Updated talk slides for 29Apr2020 talk.
2020-04-27 Mucking around with KiCAD symbol libraries.
2020-04-29 Improved the master_merge script a little.
2020-04-29 Updated encoder boards to be rendered in Fuchsia instead of PaleGreen.
2020-04-29 Turned off debugging in show script.
2020-05-03 Added a bunch of code to round the corners on the PCB. The rounding of an arc to an edge was particularly challenging.
2020-05-03 Fixed notes at aned of hr2_install.
2020-05-03 Refactored some code from hr2_models.py to scad.py.
2020-05-03 Added checkout target to mechanical/Makefile .
2020-05-07 Lots of work generating KiCad footprints.
2020-05-09 Broke the master PCB into a center/ne/nw/se/sw PCB's.
2020-05-09 Refactoring more code, This is just a safety snap-shot.
2020-05-09 More clean up of the master board PCB.
2020-05-09 Rounded the right angle corners.
2020-05-10 Wrapped up rounding the corners.
2020-05-11 Started the refactoring of rectangular connectors with footprints and components.
2020-05-13 Added module lookup to ScadProgram.
2020-05-17 Got hole placement with new PCB architecture to start working; more cleanup required.
2020-05-18 Removed a whole bunch of dead code.
2020-05-23 Converted Other_Pi board over to PCB interface.
2020-05-24 Continuing to work on converting MasterBoard to PCB interface.
2020-05-24 Both RaspberryPi3 and OtherPi are now clean classes with no outside dependencies.
2020-05-24 Reorigined RaspberryPi3 to have its origin at the center of the mount holes.
2020-05-25 Rounded the corners on EcoderBoard.
2020-05-25 EncoderBoard=>Encoder .
2020-05-25 Fixed Kicad Footprint.hole() to do oval pads correctly.
2020-05-26 Converted STLink to use PCB interface.
2020-05-31 Sonars seem to be free of mechanical interference now.
2020-05-31 Removed master_pcb_polygon inside of MasterBoard.__init_().
2020-06-03 Converted connectors_create() into Connectors class.
2020-06-03 Pass connectors object to the various places that use them.
2020-06-06 Added X/Y mirror methods to Pads.
2020-06-06 Added encoder schematic sysbol to encoder (rev. A) schematic.
2020-06-08 Got first footprint installed in encoder.kicad_pcb. PCBChunks are starting to work.
2020-06-10 Got initial pin header connector artwork working. Needs more work.
2020-06-10 Wrapped up encoder/rev_a it should be ready for schematic capture and wiring.
2020-06-13 Created the master, center, ne, nw, se, sw Kicad Projects.
2020-06-14 Added parent functionality to PCBChunk.
2020-06-14 Added Reference type.
2020-06-14 Generate Sonar footprints; added a bunch of untracked files that should be tracked.
2020-06-17 Merged Kicad.py into hr_models.py .
2020-06-19 Continued to work on KiCad footprint placement.
2020-06-21 Locked down a minimal version ne.kicad_pcb .
2020-06-21 Another manually generate ne.kicad_pcb for debugging purposes.
2020-06-22 Manually put CN60 on the back surface; need to get softare capable of doing the same.
2020-07-11 Finally sonars placed. Had to manually specify the rotattions thought.
2020-07-11 Added scad_show to bin directory.
2020-07-12 Fixed the center PCB to be generated by PCBChunks.
2020-07-12 The PCBChunk'ification of Sonars is complete.
2020-07-14 Added Raspbery Pi F2x20 Connector to schematic library.
2020-07-16 Got Raspi4B implemented as a PCB Chunk along with the mating PCBChunk.
2020-07-18 Ensure that RasPi board stays centered at origin.
2020-07-19 Got the ST Link and Adaptor converted over to CBChunk.
2020-07-20 ST Mate is automatically placed on the center.kicad_pcb.
2020-07-25 Phase 1 of PCB class removal is complete.
2020-07-27 More progress assemblies; things fit together much better now.
2020-07-29 Added LED's.
2020-07-31 Deleted a bunch of stale code mostly dealing with the old PCB class.
2020-08-01 Added 2 MikroBus click boards and 5v-to-9V Boost board.
2020-08-02 Updated Spacer class.
2020-08-02 Converted HR2BaseAssembly to use RomiBase.spacer_positions_get().
2020-08-02 Added RomiExpansionPlate.spacer_positions_get().
2020-08-02 Disabled the old key table based spacer code in MasterBoard.spacers_install().
2020-08-03 Moved a bunch of spacers around.
2020-08-03 Moved spacers around to improve support arm plate better.
2020-08-08 Added 6 Grove module locations.
2020-08-09 Added spacer mounting holes to schematics and associated PCB's.
2020-08-09 Fixed Groves and added MikroBus's.
2020-08-10 Updated the artwork for the ST Link.
2020-08-12 Got the NUCLEO placed. Readjusted a few other parts.
2020-08-16 Got Bridge connectors installed on PCB's. Tweaking still required.
2020-08-16 More work on zones (close, but not quite there yet.)
2020-08-17 More zone testing.
2020-08-18 Layed out SW PCB.
2020-08-20 Preparing to start SE PCB.
2020-08-21 Did initial SE board layout. Passes DRC.
2020-08-23 Found and fixed nasty bug in Square class.
2020-08-23 Moved Encoder connectors out by .127mm.
2020-08-24 Wrapped up NE PCB.
2020-08-26 Wrapped up STAdapter PCB.
2020-08-30 Started working on center board PCB. Clean up stale schematics.
2020-08-31 Mostly wrapped up power supply and motor driver schematics.
2020-09-05 Added some notes to electrical/README.md.
2020-09-07 Added level shifting to Sonars. Added shift register for LED's.
2020-09-09 Added servo connectors.
2020-09-14 Did major clean-up on pins_bind.py.
2020-09-20 HR2 Added Cube Project.
2020-09-21 Updated signal_bindings table in pinsbind.py to allow shorts.
2020-09-26 Continued work to bind UART'S, SPI's, and I2C peripherals.
2020-09-26 Refactored pinsbind.py in preparation of doing peripheral iteration.
2020-09-27 All of the major peripherals are allocated.
2020-09-28 Fixed some comments in pinsbind.py
2020-10-03 Linked the NE/NW/SE/SW sheets to master_board.
2020-10-04 Reworked Sonars, Servers, and LED's schematics.
2020-10-04 Renamed sonars_leds.sch to sonars_servers.sch .
2020-10-11 Cleaned up schematics some.
2020-10-17 Added WOWBus Schematic Sheet.
2020-10-18 Wrapped up SBC sheet.
2020-10-24 Schematic is basically complete.
2020-10-25 Minor tweaks prior to reannotate.
2020-10-25 Assigned PCB footprints.
2020-10-26 EMACS formater is confused, avoid issues by changing code.
2020-10-27 Got the spacer holes placed onto the PCB.
2020-10-28 Flipped Grove and Mikrobus connectors to the back side.
2020-11-03 Lots of work on the PCB.
2020-11-07 More PCB layout.
2020-11-07 More work on NW quadrant of PCB.
2020-11-09 Weaving traces from NE corner around the heat sink holes.
2020-11-13 The rats nest is getting stomped into nothingness.
2020-11-15 No unconnected traces. Outer PCB polygon has 1 extra segment.
2020-11-15 More work on ground planes.
2020-11-16 Added power test points/shunt/LED's.
2020-11-16 Worked on WOWBus TO DO list.
2020-11-18 More work on raspi display electronics.
2020-11-18 Added RasPi Display On/Off Circuit.
2020-11-21 Got servo current/possition stuff merged in.
2020-11-23 Did a design review document. Added .pdf to repository.
2020-11-29 Switched from x166 to x165 shift registers. Add bin/spi_sim.py.
2020-12-05 Removed front/back ground outline generation; Use Rectangles instead.
2020-12-06 Ground plane clean.
2020-12-06 Add USB/PWRPFET to symbol libraries.
2020-12-07 Worked on Power supply.
2020-12-09 Moved Power Supply.
2020-12-10 Changed bypass caps size from 1608 to 1005
2020-12-12 Added to_do.md
2020-12-12 Added id pins to Lidar.
2020-12-13 Got Schematic and PCB syncronized again.
2020-12-17 Worked on JLCPCB BOM generation.
2020-12-17 Added some cost estimating.
2020-12-20 Made various changes from to_do.md
2020-12-21 Fixing DRC errors.
2020-12-21 Added JLCPCB position CVS file generation.
2020-12-24 Fixed SN74C596 schematic symbol.
2020-12-24 Moved the 3.3V Regulator.
2020-12-25 Gave LED's their own ground return. Cleaned up Silk layer.
2020-12-25 Corrected Optorelay current resistors.
2020-12-25 Fixed I2C pull-ups on RasPi.
2020-12-26 NW trace cleanup complete.
2020-12-26 SW Trace clean-up.
2020-12-26 Trace cleanup complete.
2020-12-26 Switched Encoders to 5V.
2020-12-26 Added board documentation.
2020-12-27 PCB complete?
2020-12-29 Added ld06_adapter/rev_a.
2020-12-30 Rotated components for JLCPCB.
2020-12-31 Ordered Parts from Digi-Key/Newark/Amazon.
2021-01-01 Created new workspace for blinky
2021-01-01 New hr2_workspace (take two)
2021-01-04 Wrote detailed notes on configuring the blinky program in softare/README.md.
2021-01-10 Moved software/non_ide to software_old/non_ide.
2021-01-10 Continued software cleanup.
2021-01-10 Fixed some problems in software README.md.
2021-01-10 Fixed some grammar in software/README.md.
2021-01-12 Tweak software/blinky to not keep .mxproject.
2021-01-12 Fixed software/blinky/.gitignore .
2021-01-21 Started .../orders/order2/ directory.
2021-01-21 Started encoder/rev_b/ directory.
2021-01-21 Started st_adapter/rev_b/ directory.
2021-01-24 Added mechancial/spacers.py to compute spacer stacks.
2021-01-24 Added Stack to spacers.py.
2021-01-24 Added some more searches to spacers.py.
2021-01-30 No longer updated board outlines of encoder, master_board, and st_adapter.
2021-02-15 Generated st_adapter/rev_c.
2021-02-15 Added wow_fix/rev_a PCB.
2021-03-09 Random collection of file changes.
2021-03-13 Created Rev. A Sonar Adapter PCB.
2021-03-21 Updated software/README.md .
2021-03-22 Added 'software/hr2-leds-test'
2021-03-27 Updated software/README with some usbip notes.
2021-03-28 Added bin/xstm32cubeide .
2021-03-29 Wrapped up Encoder Rev. C.
2021-03-31 Added more testing programs and made edits to rev_c enocder
2021-04-02 Added bin/usbipd.service{,.sh} .
2021-04-02 Fixed usbip instructions in software/README.md.
2021-04-03 Created electrical/sonar_adapter/rev_a gerber/drill/zip files.
2021-04-03 Added electrical/wow_fix/rev_a gerber/drill/zip files.
2021-04-04 Changes to software/motor-test to do proper ESTOP clear
2021-04-12 Added encoder Rev. D. Minor changes to motor-test.
2021-04-15 Add bin/freertos_install.sh
2021-04-18 Worked on motors/encoders.
2021-04-23 Updated software/README.md
2021-04-26 Added very experimental bin/splice.py program.
2021-04-27 Tweaked software/README and uros install scripts.
2021-05-01 Updated software/blinky to stm32cubeide 1.6.0.
2021-05-01 Modified software tests to disable motors on start-up.
2021-05-02 Added software/hr2-usart-test.
2021-05-07 Got USART3_RX to work in DMA mode.
2021-05-09 Updated bin/uros_nucleo_install.sh to install some needed tools.
2021-05-24 Updated usbip stuff, tweaked software/examples.
2021-05-24 More work on USB IP.
2021-06-06 Updated bin/uros_linux_install.sh
2021-06-17 Updated bin/ros2_examples.sh and bin bin/ws_update.py .
2021-06-26 More work on software/serial_agent_generator.py.
2021-07-06 Added serial_agent_generator/README.md.
2021-07-11 software/serial_agent.py is fully refactored.
2021-07-17 software/serail_agent.py full packet encode/decode working.
2021-07-20 software/serial_agent.py serial line reader/writer threads added.
2021-07-21 softwares/erial_agent.py reordered argument parsing code.
2021-07-22 softaware/.../serial_agent.py: Converted from escaped to non-escaped paratial packets.
